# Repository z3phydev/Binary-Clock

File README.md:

# Binary Clock
## What is it?
A binary clock is a digital clock that displays the time using binary numbers instead of traditional digits. Each column represents a digit of time, so the first column is the Tens Dight of the hours, and every LED vertically is a number in binary format.
## Why did I make it?
I was originally inspired by seeing a software demo by the YouTube channel, Figuring Things Out. I wanted to try creating something similar but as a physical desk clock. The result is a clock that most people can't read but find cool. I like how the exposed PCB give it even more of that digital aesthetic.

## PCB

## PCB and Stand Render

## Schematic

## BOM

|Reference                                                                      |Qty|Value/Description|MFR               |MFR No.                |Mouser No.          |Datasheet                                                                    |Unit Price GBP|Total Price GBP|Note                                                  |FIELD11 |FIELD12               |FIELD13        |
|-------------------------------------------------------------------------------|---|-----------------|------------------|-----------------------|--------------------|-----------------------------------------------------------------------------|--------------|---------------|------------------------------------------------------|--------|----------------------|---------------|
|A1                                                                             |1  |Raspberry Pi Pico|Raspberry Pi      |SC0915                 |358-SC0915          |https://datasheets.raspberrypi.com/pico/pico-datasheet.pdf                   |4.8           |4.8            |If you want the headers you will need to buy elsewhere|        |                      |               |
|D1,D2,D3,D4,D5,D6,D7,D8,D9,D10,D11,D12,D13,D14,D15,D16,D17,D18,D19,D20         |20 |RED LED          |Cree LED          |C5SMF-RJF-CT0W0BB2     |941-C5SMFRJFCT0W0BB2|~                                                                            |0.116         |2.32           |                                                      |        |                      |               |
|J1                                                                             |1  |USB C            |GCT               |USB4085-GF-A           |640-USB4085-GF-A    |https://www.usb.org/sites/default/files/documents/usb_type-c.zip             |0.643         |0.643          |                                                      |        |                      |               |
|Q1,Q2,Q3,Q4,Q5,Q6,Q7,Q8,Q9,Q10,Q11,Q12,Q13,Q14,Q15,Q16,Q17,Q18,Q19,Q20         |20 |NPN Transistor   |onsemi / Fairchild|BC547BBU               |512-BC547BBU        |https://ngspice.sourceforge.io/docs/ngspice-html-manual/manual.xhtml#cha_BJTs|0.098         |1.96           |                                                      |        |                      |               |
|R1,R2                                                                          |2  |5.1kOhm Resistor |KOA Speer         |MF1/4DCT52R5101F       |660-MF1/4DCT52R5101F|~                                                                            |0.085         |0.17           |                                                      |        |                      |               |
|R3,R4,R5,R6,R7,R8,R9,R10,R11,R12,R13,R14,R15,R16,R17,R18,R19,R20,R21,R22       |20 |154Ohm Resistor  |Vishay / Beyschlag|MBA02040C1540FRP00     |594-MBA02040C1540FRP|~                                                                            |0.057         |1.14           |                                                      |        |                      |               |
|R23,R24,R25,R26,R27,R28,R29,R30,R31,R32,R33,R34,R35,R36,R37,R38,R39,R40,R41,R42|20 |1.18kOhm Resistor|YAGEO             |MFR-25FRF52-1K18       |603-MFR-25FRF52-1K18|~                                                                            |0.029         |0.58           |                                                      |        |                      |               |
|SW1                                                                            |1  |Button           |Same Sky          |TS02-66-70-BK-260-LCR-D|179-TS026670BK260LCR|~                                                                            |0.73          |0.7            |                                                      |        |                      |               |
|U1                                                                             |1  |DS3231 RTC Module|WINGONEER         |ASIN : B01H5NAFUY      |                    |http://datasheets.maximintegrated.com/en/ds/DS3231.pdf                       |3.99          |3.99           |Amazon link : https://amzn.eu/d/fGpd2tB               |        |                      |               |
|                                                                               |   |                 |                  |                       |                    |                                                                             |              |               |                                                      |        |Total Price USD approx|Total Price GBP|
|                                                                               |   |                 |                  |                       |                    |                                                                             |              |               |                                                      |Items   |15.06                 |11.51          |
|                                                                               |   |                 |                  |                       |                    |                                                                             |              |               |                                                      |Shipping|20.28                 |15.5           |
|                                                                               |   |                 |                  |                       |                    |                                                                             |              |               |                                                      |Finnal  |35.34                 |27.01          |

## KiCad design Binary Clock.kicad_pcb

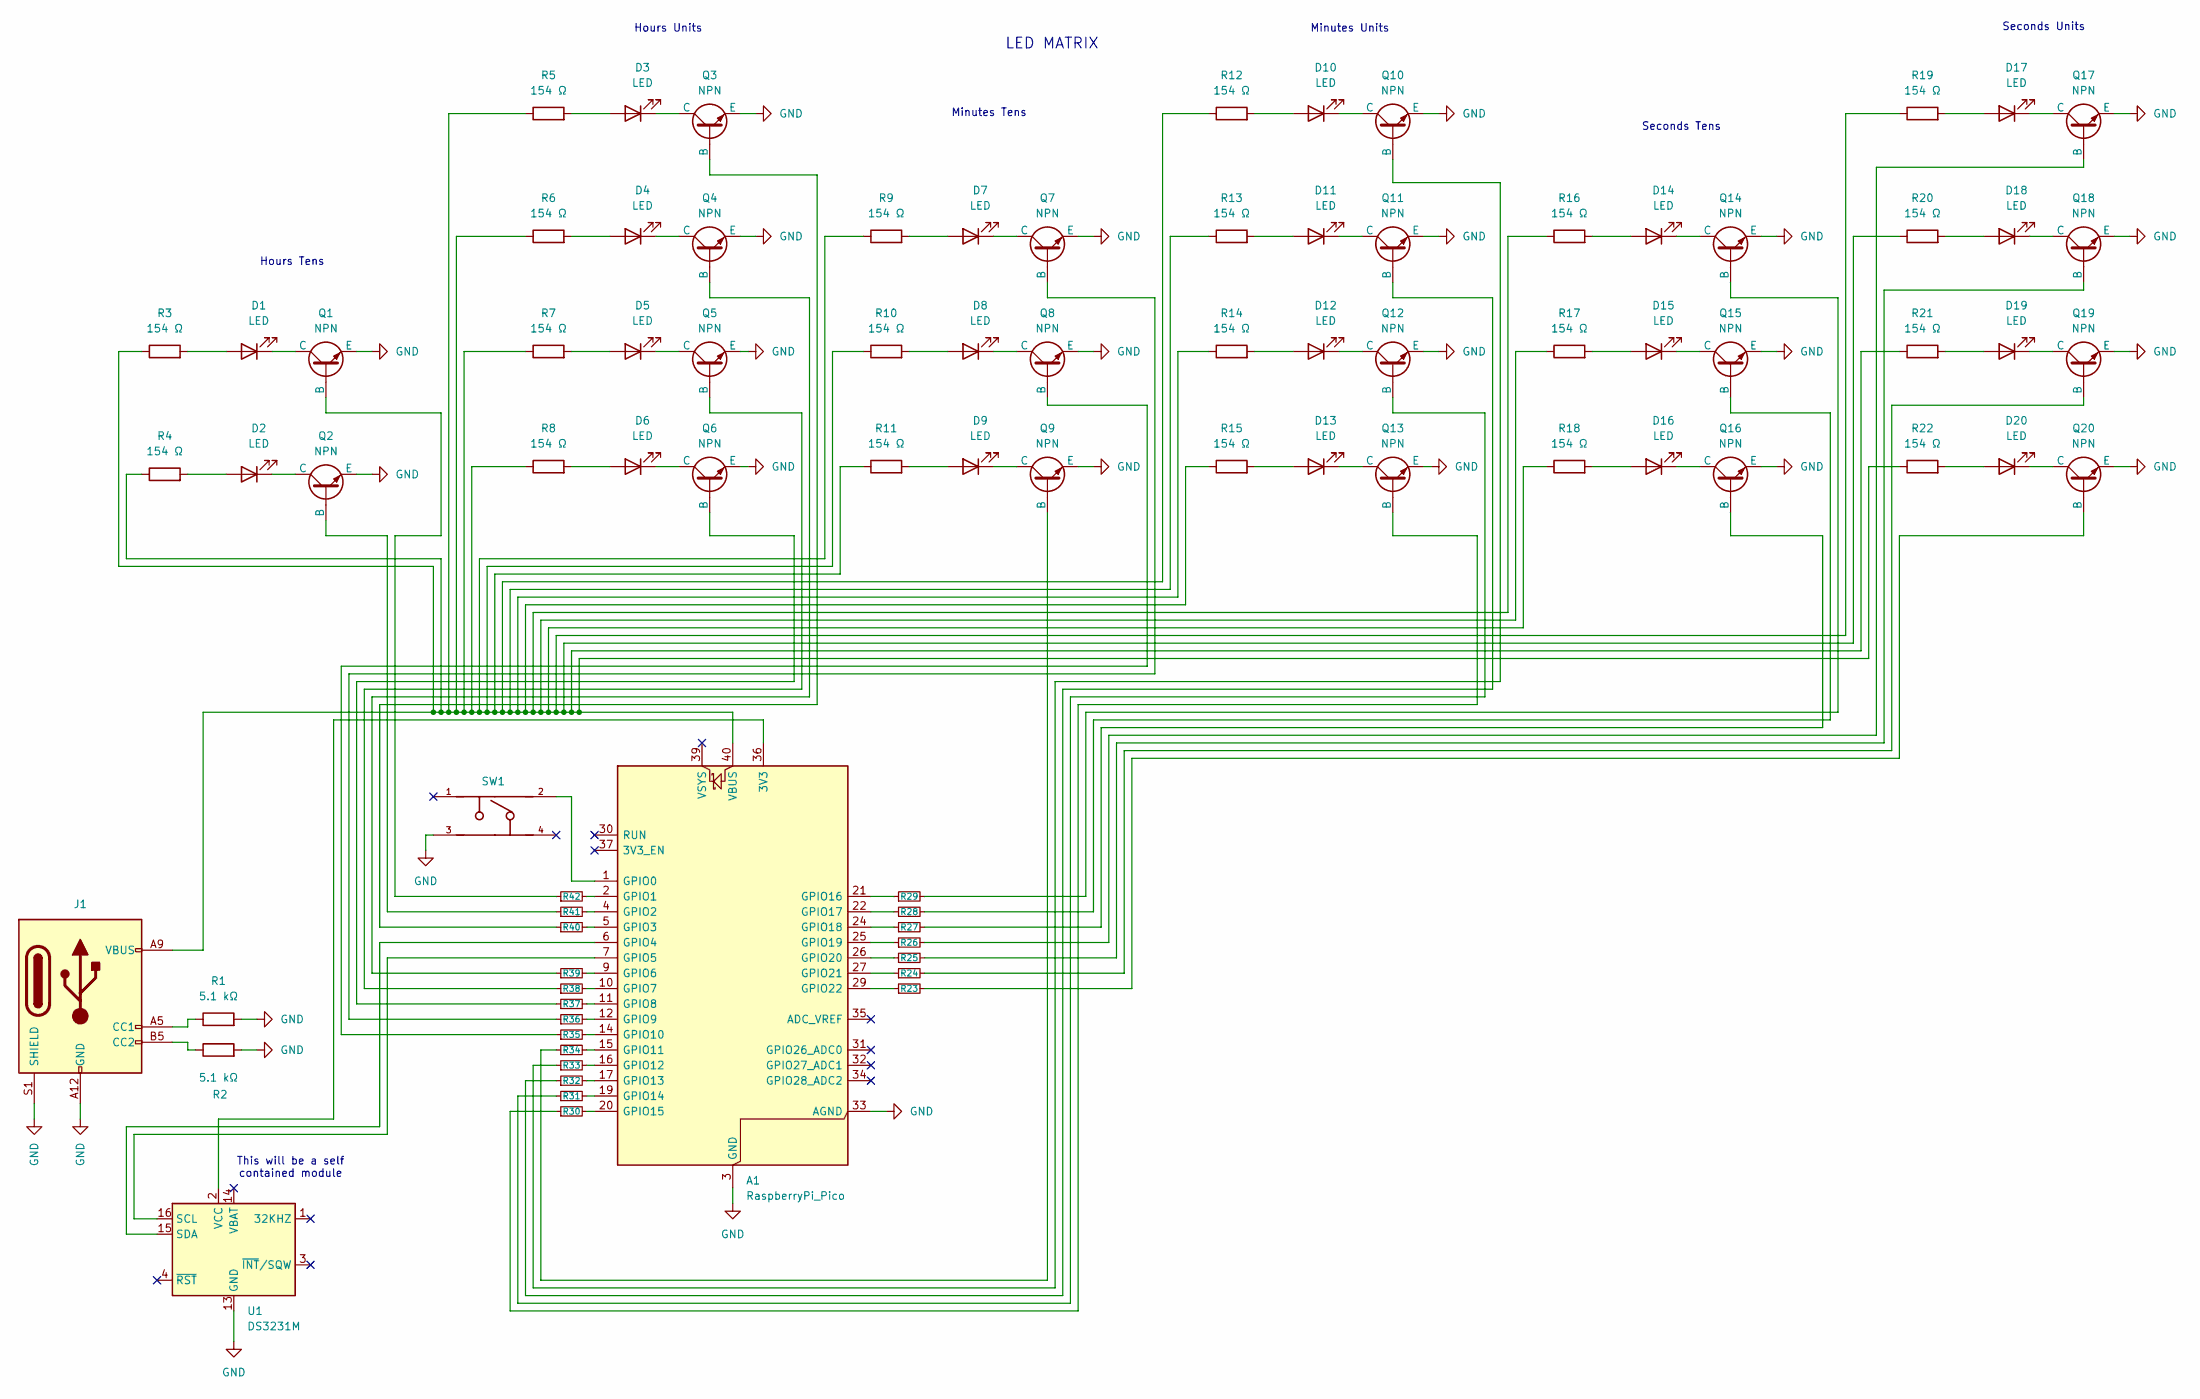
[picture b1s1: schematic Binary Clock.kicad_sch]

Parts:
A1: RaspberryPi_Pico; RaspberryPi_Pico_Common_THT
D1, D2, D3, D4, D5, D6, D7, D8, D9, D10, D11, D12, D13, D14, D15, D16, D17, D18, D19, D20: LED; LED_D5.0mm
J1: USB_C_PowerOnly; GCT_USB4085-GF-A_REVA4
Q1, Q2, Q3, Q4, Q5, Q6, Q7, Q8, Q9, Q10, Q11, Q12, Q13, Q14, Q15, Q16, Q17, Q18, Q19, Q20: NPN; TO92127P476H533-3
R1, R2: 5.1 kΩ; R_Axial_DIN0207_L6.3mm_D2.5mm_P7.62mm_Horizontal
R3, R4, R5, R6, R7, R8, R9, R10, R11, R12, R13, R14, R15, R16, R17, R18, R19, R20, R21, R22: 154 Ω; R_Axial_DIN0207_L6.3mm_D2.5mm_P7.62mm_Horizontal
R23, R24, R25, R26, R27, R28, R29, R30, R31, R32, R33, R34, R35, R36, R37, R38, R39, R40, R41, R42: R_Small; R1.18
SW1: TS02-66-70-BK-260-LCR-D; SW_TS02-66-70-BK-260-LCR-D; PARTREV 1.0
U1: DS3231M; Untitled

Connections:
GND: A1.3 (GND), A1.8 (GND), A1.13 (GND), A1.18 (GND), A1.23 (GND), A1.28 (GND), A1.33 (AGND), A1.38 (GND), J1.A12 (GND), J1.B12 (GND), J1.S1 (SHIELD), Q1.3 (E), Q2.3 (E), Q3.3 (E), Q4.3 (E), Q5.3 (E), Q6.3 (E), Q7.3 (E), Q8.3 (E), Q9.3 (E), Q10.3 (E), Q11.3 (E), Q12.3 (E), Q13.3 (E), Q14.3 (E), Q15.3 (E), Q16.3 (E), Q17.3 (E), Q18.3 (E), Q19.3 (E), Q20.3 (E), R1.2, R2.2, SW1.3, U1.5 (GND), U1.6 (GND), U1.7 (GND), U1.8 (GND), U1.9 (GND), U1.10 (GND), U1.11 (GND), U1.12 (GND), U1.13 (GND)
unnamed: A1.36 (3V3), U1.2 (VCC)
unnamed: A1.1 (GPIO0), SW1.2
unnamed: A1.2 (GPIO1), R42.2
unnamed: A1.4 (GPIO2), R41.2
unnamed: A1.5 (GPIO3), R40.2
unnamed: A1.6 (GPIO4), U1.15 (SDA)
unnamed: A1.7 (GPIO5), U1.16 (SCL)
unnamed: A1.9 (GPIO6), R39.2
unnamed: A1.10 (GPIO7), R38.2
unnamed: A1.11 (GPIO8), R37.2
unnamed: A1.12 (GPIO9), R36.2
unnamed: A1.14 (GPIO10), R35.2
unnamed: A1.15 (GPIO11), R34.2
unnamed: A1.16 (GPIO12), R33.2
unnamed: A1.17 (GPIO13), R32.2
unnamed: A1.19 (GPIO14), R31.2
unnamed: A1.20 (GPIO15), R30.2
unnamed: A1.21 (GPIO16), R29.1
unnamed: A1.22 (GPIO17), R28.1
unnamed: A1.24 (GPIO18), R27.1
unnamed: A1.25 (GPIO19), R26.1
unnamed: A1.26 (GPIO20), R25.1
unnamed: A1.27 (GPIO21), R24.1
unnamed: A1.29 (GPIO22), R23.1
unnamed: A1.40 (VBUS), J1.A9 (VBUS), J1.B9 (VBUS), R3.1, R4.1, R5.1, R6.1, R7.1, R8.1, R9.1, R10.1, R11.1, R12.1, R13.1, R14.1, R15.1, R16.1, R17.1, R18.1, R19.1, R20.1, R21.1, R22.1
unnamed: D1.2 (A), R3.2
unnamed: D1.1 (K), Q1.1 (C)
unnamed: D2.2 (A), R4.2
unnamed: D2.1 (K), Q2.1 (C)
unnamed: D3.2 (A), R5.2
unnamed: D3.1 (K), Q3.1 (C)
unnamed: D4.2 (A), R6.2
unnamed: D4.1 (K), Q4.1 (C)
unnamed: D5.2 (A), R7.2
unnamed: D5.1 (K), Q5.1 (C)
unnamed: D6.2 (A), R8.2
unnamed: D6.1 (K), Q6.1 (C)
unnamed: D7.2 (A), R9.2
unnamed: D7.1 (K), Q7.1 (C)
unnamed: D8.2 (A), R10.2
unnamed: D8.1 (K), Q8.1 (C)
unnamed: D9.2 (A), R11.2
unnamed: D9.1 (K), Q9.1 (C)
unnamed: D10.2 (A), R12.2
unnamed: D10.1 (K), Q10.1 (C)
unnamed: D11.2 (A), R13.2
unnamed: D11.1 (K), Q11.1 (C)
unnamed: D12.2 (A), R14.2
unnamed: D12.1 (K), Q12.1 (C)
unnamed: D13.2 (A), R15.2
unnamed: D13.1 (K), Q13.1 (C)
unnamed: D14.2 (A), R16.2
unnamed: D14.1 (K), Q14.1 (C)
unnamed: D15.2 (A), R17.2
unnamed: D15.1 (K), Q15.1 (C)
unnamed: D16.2 (A), R18.2
unnamed: D16.1 (K), Q16.1 (C)
unnamed: D17.2 (A), R19.2
unnamed: D17.1 (K), Q17.1 (C)
unnamed: D18.2 (A), R20.2
unnamed: D18.1 (K), Q18.1 (C)
unnamed: D19.2 (A), R21.2
unnamed: D19.1 (K), Q19.1 (C)
unnamed: D20.2 (A), R22.2
unnamed: D20.1 (K), Q20.1 (C)
unnamed: J1.A5 (CC1), R1.1
unnamed: J1.B5 (CC2), R2.1
unnamed: Q1.2 (B), R42.1
unnamed: Q2.2 (B), R41.1
unnamed: Q3.2 (B), R40.1
unnamed: Q4.2 (B), R39.1
unnamed: Q5.2 (B), R38.1
unnamed: Q6.2 (B), R37.1
unnamed: Q7.2 (B), R36.1
unnamed: Q8.2 (B), R35.1
unnamed: Q9.2 (B), R34.1
unnamed: Q10.2 (B), R33.1
unnamed: Q11.2 (B), R32.1
unnamed: Q12.2 (B), R31.1
unnamed: Q13.2 (B), R30.1
unnamed: Q14.2 (B), R29.2
unnamed: Q15.2 (B), R28.2
unnamed: Q16.2 (B), R27.2
unnamed: Q17.2 (B), R26.2
unnamed: Q18.2 (B), R25.2
unnamed: Q19.2 (B), R24.2
unnamed: Q20.2 (B), R23.2

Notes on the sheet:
This will be a self contained module
Hours Tens
Seconds Units
LED MATRIX
Minutes Units
Minutes Tens
Seconds Tens
Hours Units

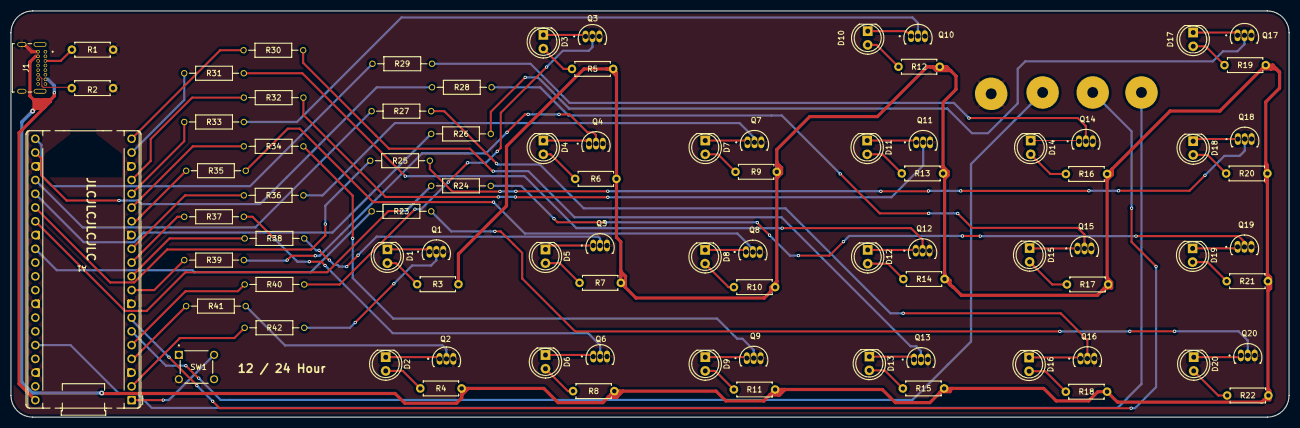
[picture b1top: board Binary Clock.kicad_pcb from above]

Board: 4 copper layers, 236.0 x 75.0 mm, 86 parts (1 on the bottom side), 88 nets.

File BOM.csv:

Reference,Qty,Value/Description,MFR,MFR No.,Mouser No.,Datasheet,Unit Price GBP,Total Price GBP,Note,,,
A1,1,Raspberry Pi Pico,Raspberry Pi,SC0915,358-SC0915,https://datasheets.raspberrypi.com/pico/pico-datasheet.pdf,4.8,4.8,If you want the headers you will need to buy elsewhere,,,
"D1,D2,D3,D4,D5,D6,D7,D8,D9,D10,D11,D12,D13,D14,D15,D16,D17,D18,D19,D20",20,RED LED,Cree LED,C5SMF-RJF-CT0W0BB2,941-C5SMFRJFCT0W0BB2,~,0.116,2.32,,,,
J1,1,USB C,GCT,USB4085-GF-A,640-USB4085-GF-A,https://www.usb.org/sites/default/files/documents/usb_type-c.zip,0.643,0.643,,,,
"Q1,Q2,Q3,Q4,Q5,Q6,Q7,Q8,Q9,Q10,Q11,Q12,Q13,Q14,Q15,Q16,Q17,Q18,Q19,Q20",20,NPN Transistor,onsemi / Fairchild,BC547BBU,512-BC547BBU,https://ngspice.sourceforge.io/docs/ngspice-html-manual/manu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,0.098,1.96,,,,
"R1,R2",2,5.1kOhm Resistor,KOA Speer,MF1/4DCT52R5101F,660-MF1/4DCT52R5101F,~,0.085,0.17,,,,
"R3,R4,R5,R6,R7,R8,R9,R10,R11,R12,R13,R14,R15,R16,R17,R18,R19,R20,R21,R22",20,154Ohm Resistor,Vishay / Beyschlag,MBA02040C1540FRP00,594-MBA02040C1540FRP,~,0.057,1.14,,,,
"R23,R24,R25,R26,R27,R28,R29,R30,R31,R32,R33,R34,R35,R36,R37,R38,R39,R40,R41,R42",20,1.18kOhm Resistor,YAGEO,MFR-25FRF52-1K18,603-MFR-25FRF52-1K18,~,0.029,0.58,,,,
SW1,1,Button,Same Sky,TS02-66-70-BK-260-LCR-D,179-TS026670BK260LCR,~,0.73,0.7,,,,
U1,1,DS3231 RTC Module,WINGONEER,ASIN : B01H5NAFUY,,http://datasheets.maximintegrated.com/en/ds/DS3231.pdf,3.99,3.99,Amazon link : https://amzn.eu/d/fGpd2tB,,,
,,,,,,,,,,,Total Price USD approx,Total Price GBP
,,,,,,,,,,Items,15.06,11.51
,,,,,,,,,,Shipping,20.28,15.5
,,,,,,,,,,Finnal,35.34,27.01

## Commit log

2025-11-08 V1 of BOM
2025-11-09 Better BOM
2025-11-09 Added README
2025-11-09 PCB step assembly
2025-11-09 Source files
2025-11-09 Kicad files
2025-11-09 .wrl upload
2025-11-09 Gerbers
2025-11-10 Added software
2025-11-10 Organising Files
2025-11-10 Create BOM
2025-11-10 Create !
2025-11-10 Untested Software
2025-11-10 3D Models Folder
2025-11-10 Step files
2025-11-10 Create Step Folder
2025-11-10 Added Render
    Added a new image of the Binary Clock to the PCB and Stand Render section.
2025-11-10 Revise README
    Updated headings and improved the description of the binary clock.
2025-11-10 Folder
2025-11-10 Add documentation for MicroPython libraries used
    Document usage of machine and utime from MicroPython.
